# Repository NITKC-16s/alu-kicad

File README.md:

# verilog alu kicad repository

Original Source is here:

- [nitkc-verilog-alu/images/いいかんじの全体図.png](https://github.com/onokatio/nitkc-verilog-alu/blob/master/images/%E3%81%84%E3%81%84%E3%81%8B%E3%82%93%E3%81%98%E3%81%AE%E5%85%A8%E4%BD%93%E5%9B%B3.png)
- [nitkc-verilog-alu/images/IMG_20191203_115229.jpg](https://github.com/onokatio/nitkc-verilog-alu/blob/master/images/IMG_20191203_115229.jpg)

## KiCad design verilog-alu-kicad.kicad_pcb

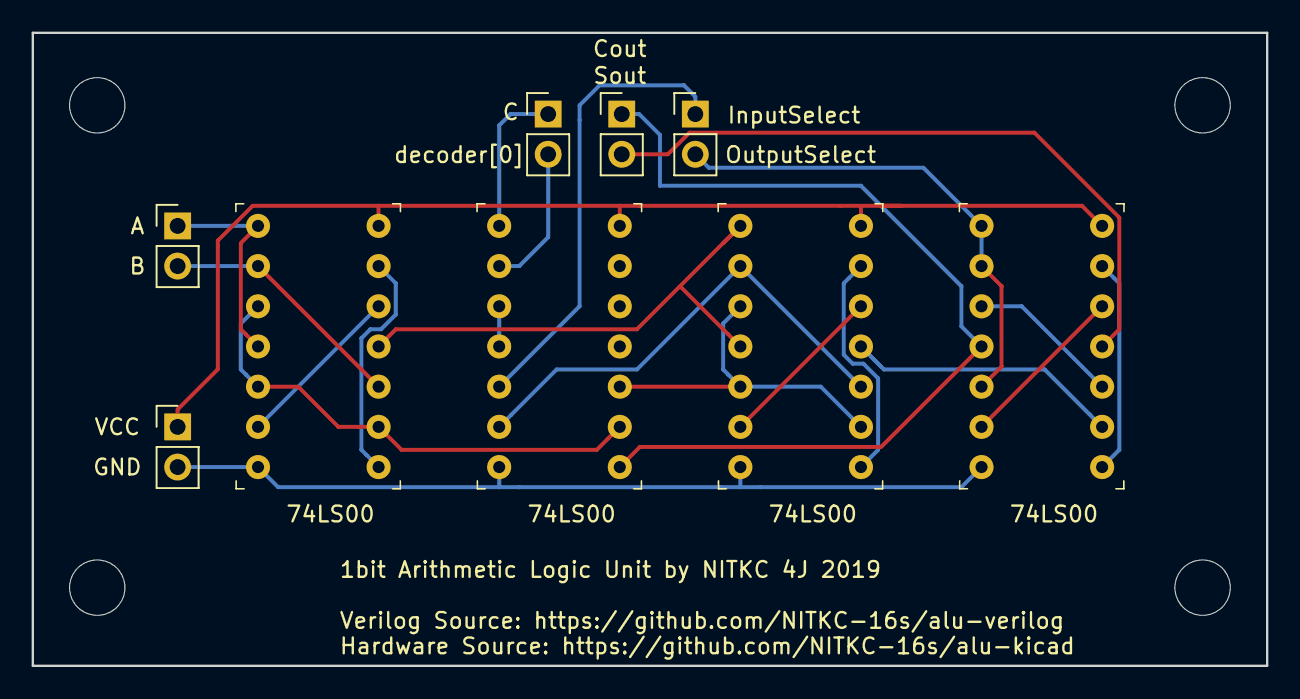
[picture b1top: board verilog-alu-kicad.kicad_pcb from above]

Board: 2 copper layers, 78.0 x 40.0 mm, 9 parts (0 on the bottom side), 23 nets.

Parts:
A&B1: Conn_01x02; PinHeader_1x02_P2.54mm_Vertical
C&decoder_0: Conn_01x02; PinHeader_1x02_P2.54mm_Vertical
Cout&Sout1: Conn_01x02; PinHeader_1x02_P2.54mm_Vertical
InputSelector&OutputSelector1: Conn_01x02; PinHeader_1x02_P2.54mm_Vertical
JVCC&GND1: Conn_01x02; PinHeader_1x02_P2.54mm_Vertical
NAND-IC-1, NAND-IC-2, NAND-IC-3, NAND-IC-4: 74LS00; Socket_DIP-14_7.62mm_Conn

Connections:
unnamed: A&B1.1, NAND-IC-1.1, NAND-IC-1.4
unnamed: A&B1.2, NAND-IC-1.2, NAND-IC-1.10
unnamed: C&decoder_0.1, NAND-IC-3.1
unnamed: C&decoder_0.2, NAND-IC-3.2
unnamed: Cout&Sout1.1, NAND-IC-3.8, NAND-IC-4.4
unnamed: Cout&Sout1.2, NAND-IC-4.11
unnamed: InputSelector&OutputSelector1.1, NAND-IC-3.5
unnamed: InputSelector&OutputSelector1.2, NAND-IC-4.1, NAND-IC-4.2, NAND-IC-4.5
unnamed: JVCC&GND1.1, NAND-IC-1.14, NAND-IC-2.14, NAND-IC-3.14, NAND-IC-4.14
unnamed: JVCC&GND1.2, NAND-IC-1.7, NAND-IC-2.7, NAND-IC-3.7, NAND-IC-4.7
unnamed: NAND-IC-1.3, NAND-IC-1.5, NAND-IC-1.9, NAND-IC-3.9
unnamed: NAND-IC-1.11, NAND-IC-2.1, NAND-IC-2.4
unnamed: NAND-IC-1.6, NAND-IC-1.12
unnamed: NAND-IC-1.8, NAND-IC-1.13
unnamed: NAND-IC-2.3, NAND-IC-2.5, NAND-IC-2.9, NAND-IC-3.10
unnamed: NAND-IC-2.2, NAND-IC-2.10, NAND-IC-3.6
unnamed: NAND-IC-2.11, NAND-IC-4.9
unnamed: NAND-IC-2.6, NAND-IC-2.12
unnamed: NAND-IC-2.8, NAND-IC-2.13
unnamed: NAND-IC-3.3, NAND-IC-3.4
unnamed: NAND-IC-4.3, NAND-IC-4.10
unnamed: NAND-IC-4.6, NAND-IC-4.12
unnamed: NAND-IC-4.8, NAND-IC-4.13

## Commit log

2019-12-10 init
2019-12-10 Add .whitesource configuration file
2019-12-10 add readme
2019-12-10 implement power supply
2019-12-10 add image
2019-12-10 [ImgBot] Optimize images
    /eschema-overview.png -- 22.83kb -> 12.97kb (43.2%)
2019-12-10 １ピンの接続点を２ピンに変更
2019-12-10 Restyled by whitespace
2019-12-11 add gitignore and remove unneeded file
2019-12-17 change pin name & add footprint
2019-12-17 add pcb
2019-12-24 fix pin
2019-12-24 try wiring
2020-01-02 完成したんじゃね？
2020-01-29 update for print
2020-01-29 image
2020-01-29 set origin and frame line
